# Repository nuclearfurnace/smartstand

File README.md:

# What is the SmartStand?

The SmartStand is a headphone stand that features not only a built-in, high-quality USB DAC and headphone amplifier, but the ability to detect when your headphones are in use (off the stand) and automatically switch between headphone output and line out, all while presenting as a normal USB audio device to your computer.

# What are the specifications?  How does it sound?

I'm not sure yet!  I haven't reached a rev A for the final design.  Here's the rough breakdown of what the design has:

- XMOS processor for the USB controller ([datasheet](https://www.xmos.com/download/private/XUF208-256-TQ64-Datasheet%281.10%29.pdf), can support UAC2 up to 384kHz at 2 channels)
- TI [PCM5102A](http://www.ti.com/lit/ds/symlink/pcm5102a.pdf) for the DAC
- low-noise power supplies
    - 12V DC wall wart which feeds
        - a TI [TPS563200](http://www.ti.com/lit/ds/symlink/tps563200.pdf) synchronous step-down converter which feeds
            - a TI [TPS7A8300](http://www.ti.com/lit/ds/symlink/tps7a8300.pdf) which provides the 1V0 core supply
        - a TI [TPS563200](http://www.ti.com/lit/ds/symlink/tps563200.pdf) synchronous step-down converter which feeds
            - a TI [TPS7A8300](http://www.ti.com/lit/ds/symlink/tps7a8300.pdf) which provides the digital 3V3 supply
            - a TI [TPS7A8300](http://www.ti.com/lit/ds/symlink/tps7a8300.pdf) which provides the analog 3V3 supply
        - a TI [TPS7A4701](http://www.ti.com/lit/ds/symlink/tps7a47.pdf) which provides the positive 11V0 amplifier rail
        - a TI [TPS7A3301](http://www.ti.com/lit/ds/symlink/tps7a33.pdf) which provides the negative 11V0 amplifier rail
- amplifier section that mirrors the [Objective2](http://nwavguy.blogspot.com/2011/07/o2-headphone-amp.html) headphone amplifier
    - an [NJM2068](http://www.njr.com/semicon/PDF/NJM2068_E.pdf)-based gain stage, with internal switches for dual gain settings
    - an Alps [RK14K](http://www.alps.com/prod/info/E/HTML/Potentiometer/RotaryPotentiometers/RK14K12/RK14K1240A4S.html) volume control pot after the gain stage, big and chunky (1B taper)
    - paralleled [NJM4556A](http://www.njr.com/semicon/PDF/NJM4556A_E.pdf)s for the output stage for lots o' power
- relay-based switching between headphone outputs and line outs, as well as relay-based protection on the headphone outputs to avoid pops and thumps
- Neutrik [NRJ6HH](http://www.neutrik.com/en/audio/plugs-and-jacks/slim-jacks/nrj6hh) 1/4" headphone jack
- Switchcraft [PJRAN2X1U01AUX](http://www.switchcraft.com/Drawings/pjran2x1u__x_series_cd.pdf) RCA outputs
- TE USB type B connector [292304-1](http://www.te.com/usa-en/product-292304-1.html)
- 0.1% precision resistors, and NP0/C0G capacitors in the audio path

# What's in this repository?

This repository will hold all the Eagle CAD design files for the internals, including:

- original, sloppy evaluation boards for the XMOS processor and amplifier section
- the integrated USB DAC/amplifier board (single board that will be used in the unit)
- proximity sensor board (will be located in the stand arm where the headphones rest)
- any schematic- or board-related design files i.e. DRC rules, 3D IDF data, etc

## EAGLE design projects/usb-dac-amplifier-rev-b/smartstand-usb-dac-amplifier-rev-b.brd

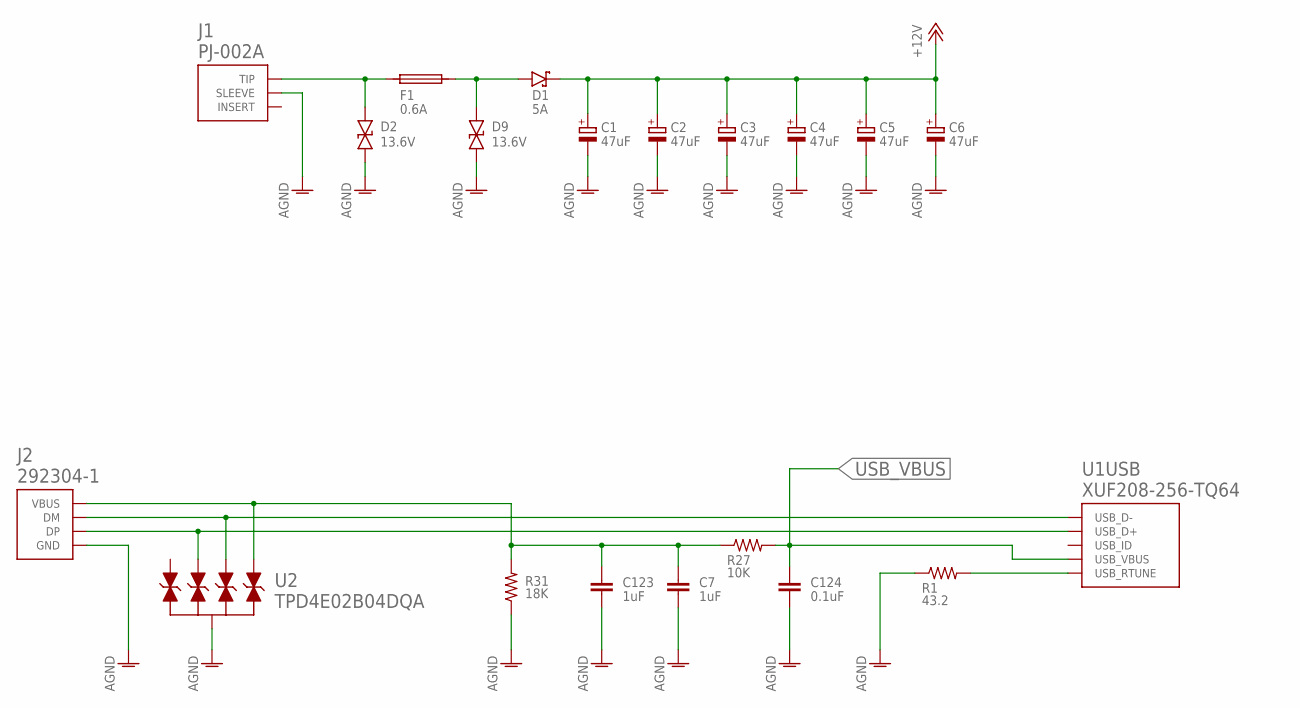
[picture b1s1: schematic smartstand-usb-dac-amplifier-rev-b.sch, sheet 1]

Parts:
C1, C2, C3, C4, C5, C6: 47uF; CHEMICON_F55
C7, C123: 1uF; C0603
C124: 0.1uF; C0402
D1: 5A; SOD128; MPN PMEG3050BEP,115
D2, D9: 13.6V; SMA; MPN P4SMA16CA
F1: 0.6A; 2920L; MPN 2920L030DR
J1: PJ-002A; VOLTAGE 12.0; MPN PJ-002A
J2: 292304-1; 292304; MPN 292304-1
R1: 43.2; R0402; MPN RK73B1ETTP430J
R27: 10K; R0402
R31: 18K; R0402
U1: XUF208-256-TQ64; TQFP-64-EXPOSED-PAD
U2: TPD4E02B04DQA; R-PUSON-N10; MPN TPD4E02B04DQAR

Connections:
+12V: C1.+, C2.+, C3.+, C4.+, C5.+, C6.+, D1.C; also elsewhere on the board
AGND: C1.-, C2.-, C3.-, C4.-, C5.-, C6.-, C7.2, C123.2, C124.2, D2.A, D9.A, J1.2 (SLEEVE), J2.P$4 (GND), R1.1, R31.1, U2.P$3 (GND), U2.P$8 (GND); also elsewhere on the board
unnamed: D2.C, F1.P$1 (1), J1.1 (TIP)
unnamed: D1.A, D9.C, F1.P$2 (2)
unnamed: R1.2, U1.P$24 (USB_RTUNE)
unnamed: C7.1, C123.1, J2.P$1 (VBUS), R27.1, R31.2, U2.P$5 (IO4), U2.P$6 (IO4)
USB_D_N: J2.P$2 (DM), U1.P$26 (USB_D-), U2.P$4 (IO3), U2.P$7 (IO3)
USB_D_P: J2.P$3 (DP), U1.P$25 (USB_D+), U2.P$2 (IO2), U2.P$9 (IO2)
USB_VBUS: C124.1, R27.2, U1.P$23 (USB_VBUS); also elsewhere on the board

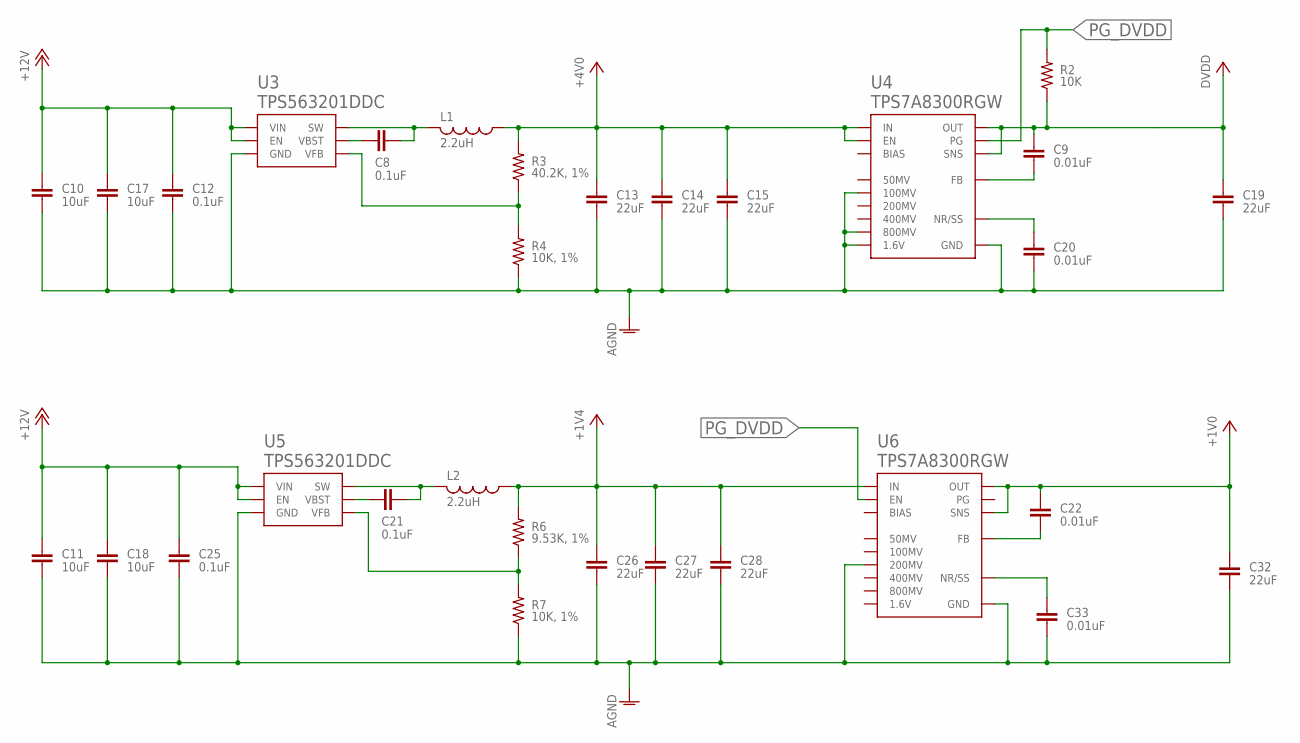
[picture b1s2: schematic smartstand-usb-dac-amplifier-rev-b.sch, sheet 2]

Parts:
C8, C21: 0.1uF; C0603; MPN GCM188R71H104KA57J
C9, C20, C22, C33: 0.01uF; C0402
C10, C11, C17, C18: 10uF; C0603; MPN GRM188R6YA106MA73D
C12, C25: 0.1uF; C0402
C13, C14, C15, C19, C26, C27, C28, C32: 22uF; C0603; MPN ZRB18AR61A226ME01L
L1, L2: 2.2uH; TDK-VLP8040; MPN VLP8040T-2R2N
R2: 10K; R0402; MPN RC0402FR-0710KL
R3: 40.2K, 1%; R0402; MPN RK73H1ETTP4022F
R4, R7: 10K, 1%; R0402; MPN RC0402FR-0710KL
R6: 9.53K, 1%; R0402; MPN RC0402FR-079K53L
U3, U5: TPS563201DDC; R-PDSO-G6-DBV; MPN TPS563201DDC
U4, U6: TPS7A8300RGW; S-PVQFN-N20; MPN TPS7A8300RGWR

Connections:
+1V0: C22.1, C32.1, U6.P$1 (OUT), U6.P$2 (SNS), U6.P$19 (OUT), U6.P$20 (OUT); also elsewhere on the board
+1V4: C26.1, C27.1, C28.1, L2.P$1 (1), R6.2, U6.P$15 (IN), U6.P$16 (IN), U6.P$17 (IN); also elsewhere on the board
+4V0: C13.1, C14.1, C15.1, L1.P$1 (1), R3.2, U4.P$14 (EN), U4.P$15 (IN), U4.P$16 (IN), U4.P$17 (IN); also elsewhere on the board
+12V: C10.1, C11.1, C12.1, C17.1, C18.1, C25.1, U3.3 (VIN), U3.5 (EN), U5.3 (VIN), U5.5 (EN); also elsewhere on the board
AGND: C10.2, C11.2, C12.2, C13.2, C14.2, C15.2, C17.2, C18.2, C19.2, C20.2, C25.2, C26.2, C27.2, C28.2, C32.2, C33.2, R4.1, R7.1, U3.1 (GND), U4.P$6 (100MV), U4.P$8 (GND), U4.P$10 (800MV), U4.P$11 (1.6V), U4.P$18 (GND), U4.P$21 (GND), U4.P$22 (GND), U4.P$23 (GND), U4.P$24 (GND), U4.P$25 (GND), U4.P$26 (GND), U4.P$27 (GND), U4.P$28 (GND), U4.P$29 (GND), U4.P$EP (GND), U5.1 (GND), U6.P$7 (200MV), U6.P$8 (GND), U6.P$18 (GND), U6.P$21 (GND), U6.P$22 (GND), U6.P$23 (GND), U6.P$24 (GND), U6.P$25 (GND), U6.P$26 (GND), U6.P$27 (GND), U6.P$28 (GND), U6.P$29 (GND), U6.P$EP (GND); also elsewhere on the board
DVDD: C9.1, C19.1, R2.1, U4.P$1 (OUT), U4.P$2 (SNS), U4.P$19 (OUT), U4.P$20 (OUT); also elsewhere on the board
unnamed: C20.1, U4.P$13 (NR/SS)
unnamed: C9.2, U4.P$3 (FB)
unnamed: C8.2, L1.P$2 (2), U3.2 (SW)
unnamed: C8.1, U3.6 (VBST)
unnamed: R3.1, R4.2, U3.4 (VFB)
unnamed: C21.2, L2.P$2 (2), U5.2 (SW)
unnamed: C21.1, U5.6 (VBST)
unnamed: R6.1, R7.2, U5.4 (VFB)
unnamed: C33.1, U6.P$13 (NR/SS)
unnamed: C22.2, U6.P$3 (FB)
PG_DVDD: R2.2, U4.P$4 (PG), U6.P$14 (EN)

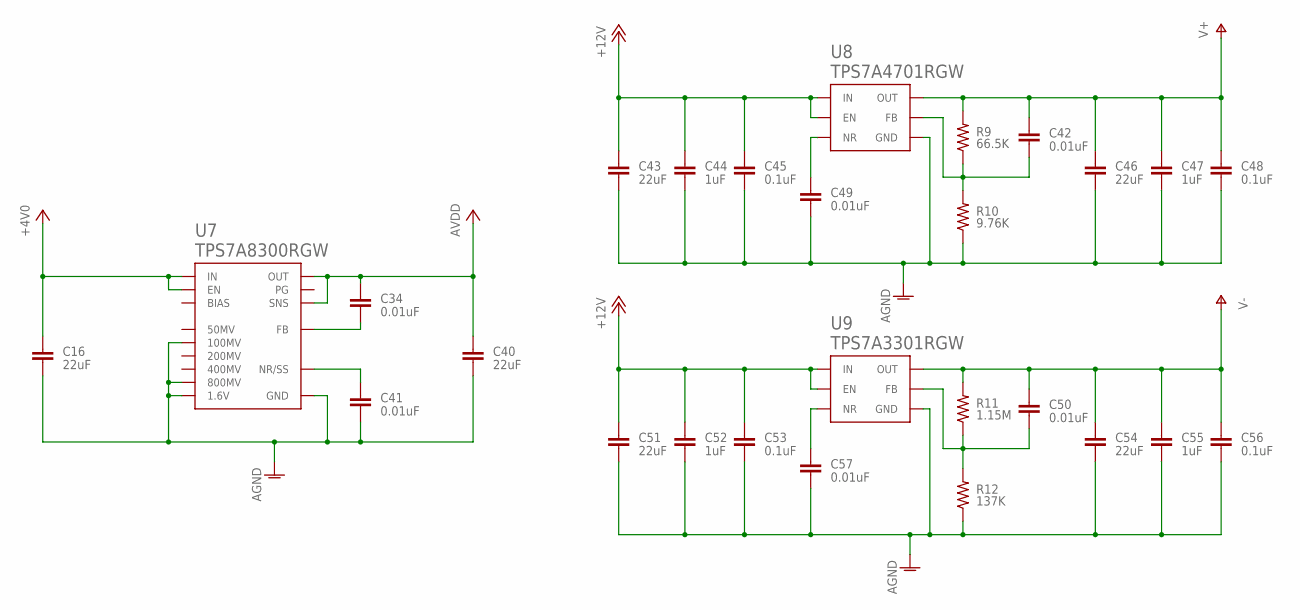
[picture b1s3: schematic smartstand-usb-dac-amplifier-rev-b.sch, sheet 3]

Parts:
C16, C40: 22uF; C0603; MPN ZRB18AR61A226ME01L
C34, C41, C42, C49, C50, C57: 0.01uF; C0402
C43, C46, C51, C54: 22uF; C0603; MPN GRM188R6YA106MA73D
C44, C47, C52, C55: 1uF; C0603
C45, C48, C53, C56: 0.1uF; C0402
R9: 66.5K; R0402; MPN RK73H1ETTP6652F
R10: 9.76K; R0402; MPN RC0402FR-079K76L
R11: 1.15M; R0402; MPN RK73H1ETTP1154F
R12: 137K; R0402; MPN RC0402FR-07137KL
U7: TPS7A8300RGW; S-PVQFN-N20; MPN TPS7A8300RGWR
U8: TPS7A4701RGW; S-PVQFN-N20; MPN TPS7A4701RGWR
U9: TPS7A3301RGW; S-PVQFN-N20; MPN TPS7A3301RGWR

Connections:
+4V0: C16.1, U7.P$14 (EN), U7.P$15 (IN), U7.P$16 (IN), U7.P$17 (IN); also elsewhere on the board
+12V: C43.1, C44.1, C45.1, C51.1, C52.1, C53.1, U8.P$13 (EN), U8.P$15 (IN), U8.P$16 (IN), U9.P$13 (EN), U9.P$15 (IN), U9.P$16 (IN); also elsewhere on the board
AGND: C16.2, C40.2, C41.2, C43.2, C44.2, C45.2, C46.2, C47.2, C48.2, C49.2, C51.2, C52.2, C53.2, C54.2, C55.2, C56.2, C57.2, R10.1, R12.1, U7.P$6 (100MV), U7.P$8 (GND), U7.P$10 (800MV), U7.P$11 (1.6V), U7.P$18 (GND), U7.P$21 (GND), U7.P$22 (GND), U7.P$23 (GND), U7.P$24 (GND), U7.P$25 (GND), U7.P$26 (GND), U7.P$27 (GND), U7.P$28 (GND), U7.P$29 (GND), U7.P$EP (GND), U8.P$7 (GND), U8.P$17 (GND), U8.P$18 (GND), U8.P$19 (GND), U8.P$21 (GND), U8.P$22 (GND), U8.P$23 (GND), U8.P$24 (GND), U8.P$25 (GND), U8.P$26 (GND), U8.P$27 (GND), U8.P$28 (GND), U8.P$29 (GND), U8.P$EP (GND), U9.P$7 (GND), U9.P$17 (GND), U9.P$18 (GND), U9.P$19 (GND), U9.P$21 (GND), U9.P$22 (GND), U9.P$23 (GND), U9.P$24 (GND), U9.P$25 (GND), U9.P$26 (GND), U9.P$27 (GND), U9.P$28 (GND), U9.P$29 (GND), U9.P$EP (GND); also elsewhere on the board
AVDD: C34.1, C40.1, U7.P$1 (OUT), U7.P$2 (SNS), U7.P$19 (OUT), U7.P$20 (OUT); also elsewhere on the board
unnamed: C57.1, U9.P$14 (NR)
unnamed: C49.1, U8.P$14 (NR)
unnamed: C42.2, R9.1, R10.2, U8.P$3 (FB)
unnamed: C50.2, R11.1, R12.2, U9.P$3 (FB)
unnamed: C41.1, U7.P$13 (NR/SS)
unnamed: C34.2, U7.P$3 (FB)
V+: C42.1, C46.1, C47.1, C48.1, R9.2, U8.P$1 (OUT), U8.P$20 (OUT); also elsewhere on the board
V-: C50.1, C54.1, C55.1, C56.1, R11.2, U9.P$1 (OUT), U9.P$20 (OUT); also elsewhere on the board

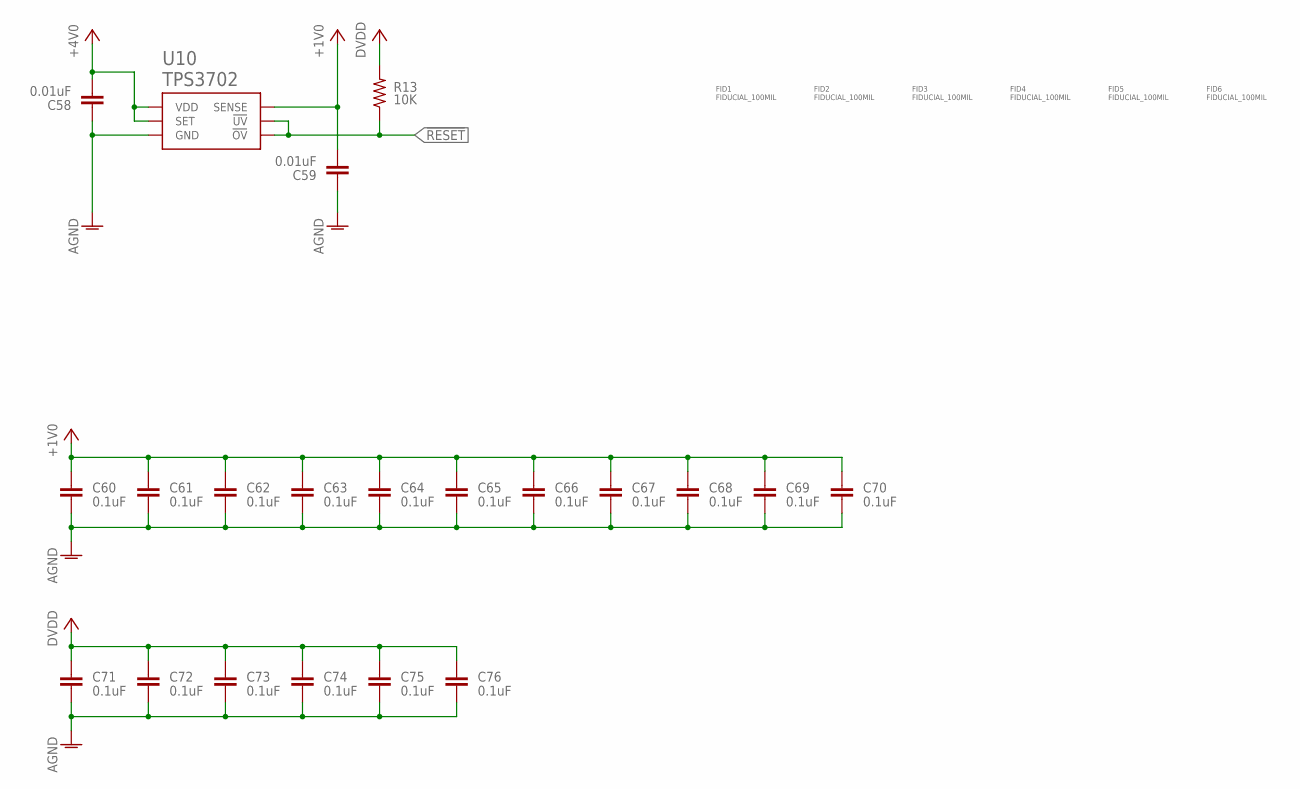
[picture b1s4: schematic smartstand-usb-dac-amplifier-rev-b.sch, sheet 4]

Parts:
C58, C59: 0.01uF; C0402
C60, C61, C62, C63, C64, C65, C66, C67, C68, C69, C70, C71, C72, C73, C74, C75, C76: 0.1uF; C0402
FID1, FID2, FID3, FID4, FID5, FID6: FIDUCIAL_100MIL
R13: 10K; R0402
U10: TPS3702; R-PDSO-G6-DBV; MPN TPS3702CX10DDCT

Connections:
!RESET: R13.1, U10.1 (!UV), U10.6 (!OV); also elsewhere on the board
+1V0: C59.2, C60.1, C61.1, C62.1, C63.1, C64.1, C65.1, C66.1, C67.1, C68.1, C69.1, C70.1, U10.3 (SENSE); also elsewhere on the board
+4V0: C58.2, U10.4 (SET), U10.5 (VDD); also elsewhere on the board
AGND: C58.1, C59.1, C60.2, C61.2, C62.2, C63.2, C64.2, C65.2, C66.2, C67.2, C68.2, C69.2, C70.2, C71.2, C72.2, C73.2, C74.2, C75.2, C76.2, U10.2 (GND); also elsewhere on the board
DVDD: C71.1, C72.1, C73.1, C74.1, C75.1, C76.1, R13.2; also elsewhere on the board

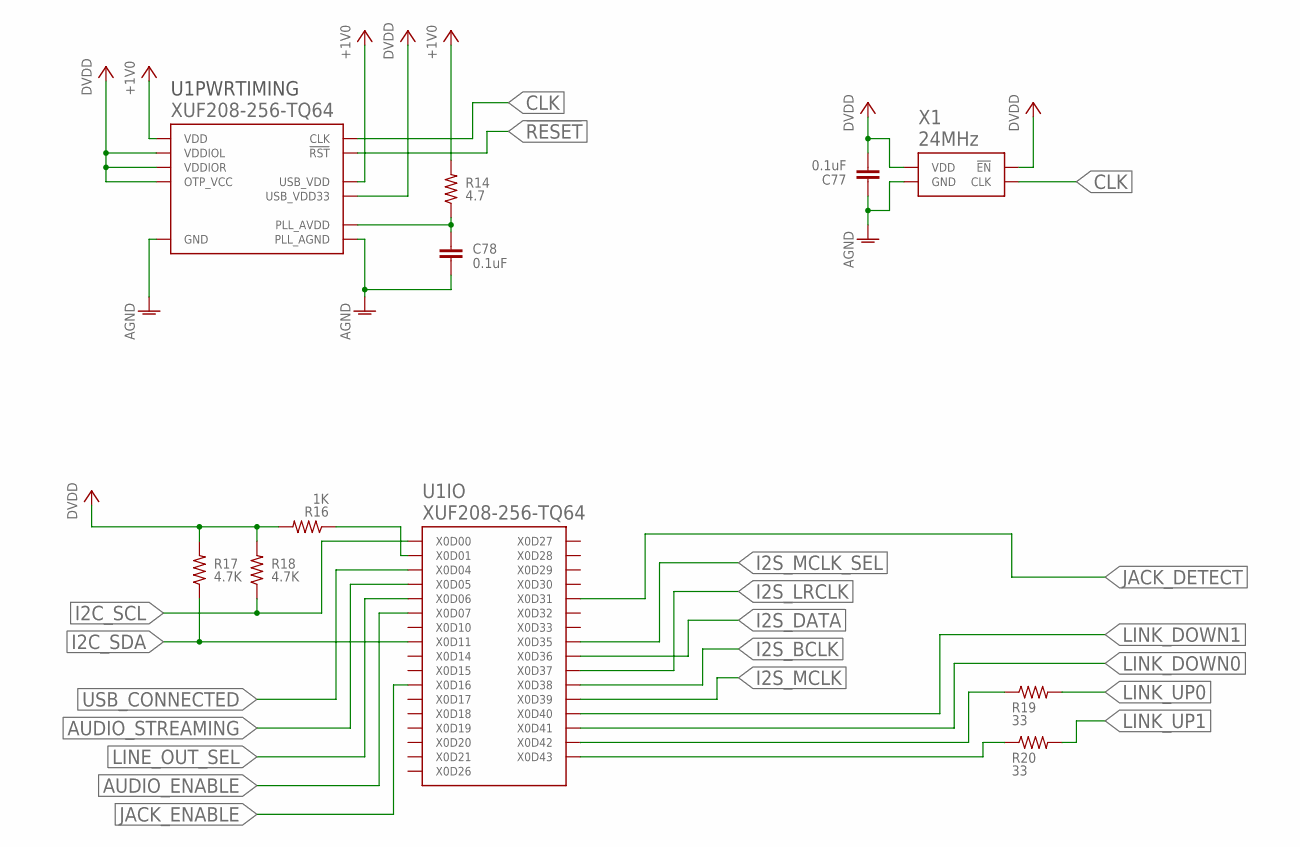
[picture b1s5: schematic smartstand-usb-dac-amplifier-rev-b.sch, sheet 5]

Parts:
C77, C78: 0.1uF; C0402
R14: 4.7; R0402; MPN RCS04024R70JNED
R16: 1K; R0402
R17, R18: 4.7K; R0402
R19, R20: 33; R0402; MPN RK73B1ETTP330J
U1: XUF208-256-TQ64; TQFP-64-EXPOSED-PAD
X1: 24MHz; KC2520C; MPN KC2520C24.0000C2LE00

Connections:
!RESET: U1.P$57 (!RST); also elsewhere on the board
+1V0: R14.2, U1.P$9 (VDD), U1.P$10 (VDD), U1.P$20 (VDD), U1.P$27 (USB_VDD), U1.P$31 (VDD), U1.P$39 (VDD), U1.P$40 (VDD), U1.P$41 (VDD), U1.P$52 (VDD), U1.P$56 (VDD), U1.P$59 (VDD); also elsewhere on the board
AGND: C77.1, C78.2, U1.P$54 (PLL_AGND), U1.P$65 (GND), U1.P$66 (GND), U1.P$67 (GND), U1.P$68 (GND), U1.P$69 (GND), U1.P$70 (GND), U1.P$71 (GND), U1.P$72 (GND), U1.P$73 (GND), U1.P$74 (GND), X1.P$2 (GND); also elsewhere on the board
AUDIO_ENABLE: U1.P$19 (X0D07); also elsewhere on the board
AUDIO_STREAMING: U1.P$17 (X0D05); also elsewhere on the board
CLK: U1.P$58 (CLK), X1.P$3 (CLK); also elsewhere on the board
DVDD: C77.2, R16.2, R17.2, R18.2, U1.P$3 (VDDIOL), U1.P$13 (VDDIOL), U1.P$22 (USB_VDD33), U1.P$34 (VDDIOR), U1.P$44 (VDDIOR), U1.P$55 (OTP_VCC), X1.P$1 (!EN), X1.P$4 (VDD); also elsewhere on the board
I2C_SCL: R18.1, U1.P$14 (X0D00); also elsewhere on the board
I2C_SDA: R17.1, U1.P$16 (X0D11); also elsewhere on the board
I2S_BCLK: U1.P$2 (X0D38); also elsewhere on the board
I2S_DATA: U1.P$1 (X0D36); also elsewhere on the board
I2S_LRCLK: U1.P$64 (X0D37); also elsewhere on the board
I2S_MCLK: U1.P$4 (X0D39); also elsewhere on the board
I2S_MCLK_SEL: U1.P$42 (X0D35); also elsewhere on the board
JACK_DETECT: U1.P$51 (X0D31); also elsewhere on the board
JACK_ENABLE: U1.P$35 (X0D16); also elsewhere on the board
LINE_OUT_SEL: U1.P$18 (X0D06); also elsewhere on the board
LINK_DOWN0: U1.P$6 (X0D41); also elsewhere on the board
LINK_DOWN1: U1.P$5 (X0D40); also elsewhere on the board
LINK_UP0: R19.2; also elsewhere on the board
LINK_UP1: R20.2; also elsewhere on the board
unnamed: R19.1, U1.P$7 (X0D42)
unnamed: R20.1, U1.P$8 (X0D43)
unnamed: R16.1, U1.P$11 (X0D01)
PLL_AVDD: C78.1, R14.1, U1.P$53 (PLL_AVDD); also elsewhere on the board
USB_CONNECTED: U1.P$15 (X0D04); also elsewhere on the board

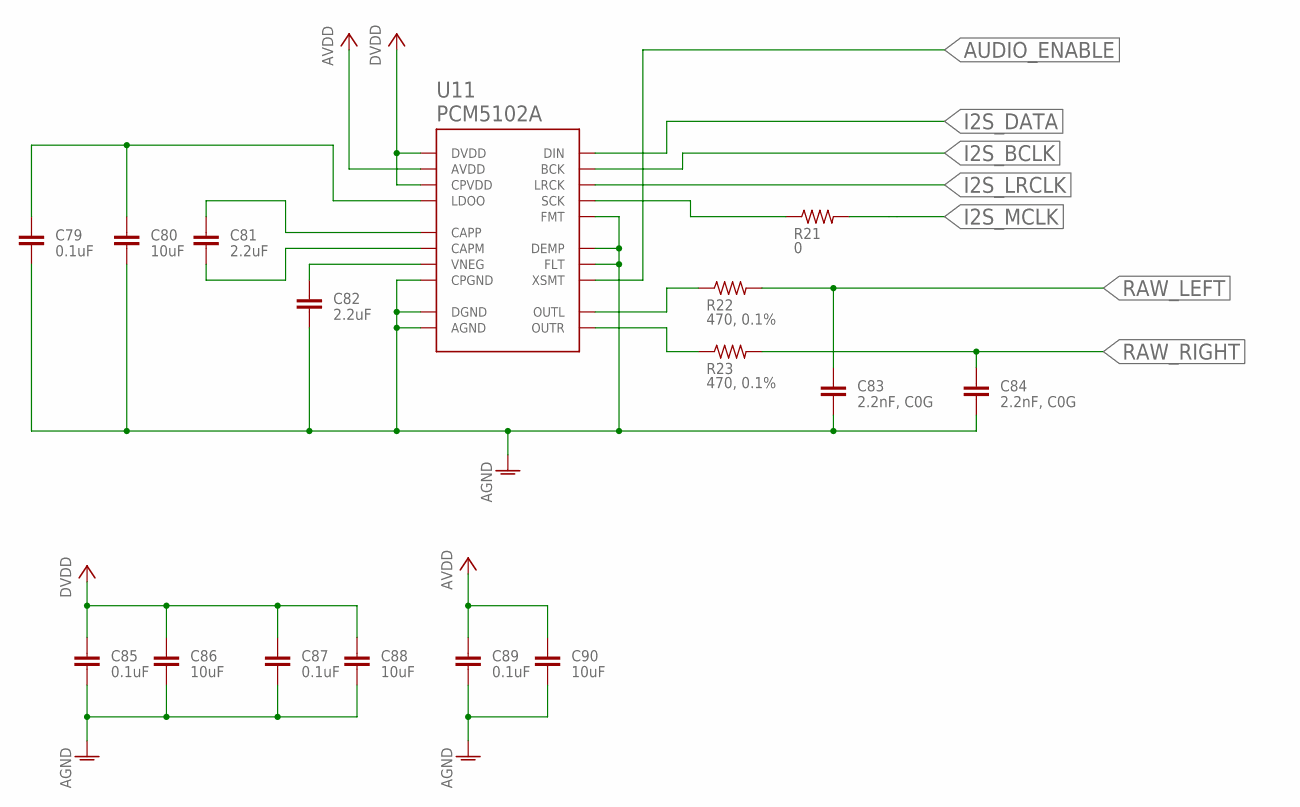
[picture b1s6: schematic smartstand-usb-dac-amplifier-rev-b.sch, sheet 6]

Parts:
C79, C85, C87, C89: 0.1uF; C0402
C80, C86, C88, C90: 10uF; C0805; MPN GRM21BR61E106KA73L
C81, C82: 2.2uF; C0603; MPN GRM188R61C225KE15D
C83, C84: 2.2nF, C0G; C0402; MPN C0402C222J3GACTU
R21: 0; R0402
R22, R23: 470, 0.1%; R0402; MPN RG1005P-471-B-T5
U11: PCM5102A; R-PDSO-G20; MPN PCM5102APWR

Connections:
AGND: C79.2, C80.2, C82.2, C83.2, C84.2, C85.2, C86.2, C87.2, C88.2, C89.2, C90.2, U11.P$3 (CPGND), U11.P$9 (AGND), U11.P$10 (DEMP), U11.P$11 (FLT), U11.P$16 (FMT), U11.P$19 (DGND); also elsewhere on the board
AUDIO_ENABLE: U11.P$17 (XSMT); also elsewhere on the board
AVDD: C89.1, C90.1, U11.P$8 (AVDD); also elsewhere on the board
DVDD: C85.1, C86.1, C87.1, C88.1, U11.P$1 (CPVDD), U11.P$20 (DVDD); also elsewhere on the board
I2S_BCLK: U11.P$13 (BCK); also elsewhere on the board
I2S_DATA: U11.P$14 (DIN); also elsewhere on the board
I2S_LRCLK: U11.P$15 (LRCK); also elsewhere on the board
I2S_MCLK: R21.2; also elsewhere on the board
unnamed: C81.1, U11.P$2 (CAPP)
unnamed: C81.2, U11.P$4 (CAPM)
unnamed: C82.1, U11.P$5 (VNEG)
unnamed: C79.1, C80.1, U11.P$18 (LDOO)
unnamed: R22.1, U11.P$6 (OUTL)
unnamed: R23.1, U11.P$7 (OUTR)
unnamed: R21.1, U11.P$12 (SCK)
RAW_LEFT: C83.1, R22.2; also elsewhere on the board
RAW_RIGHT: C84.1, R23.2; also elsewhere on the board

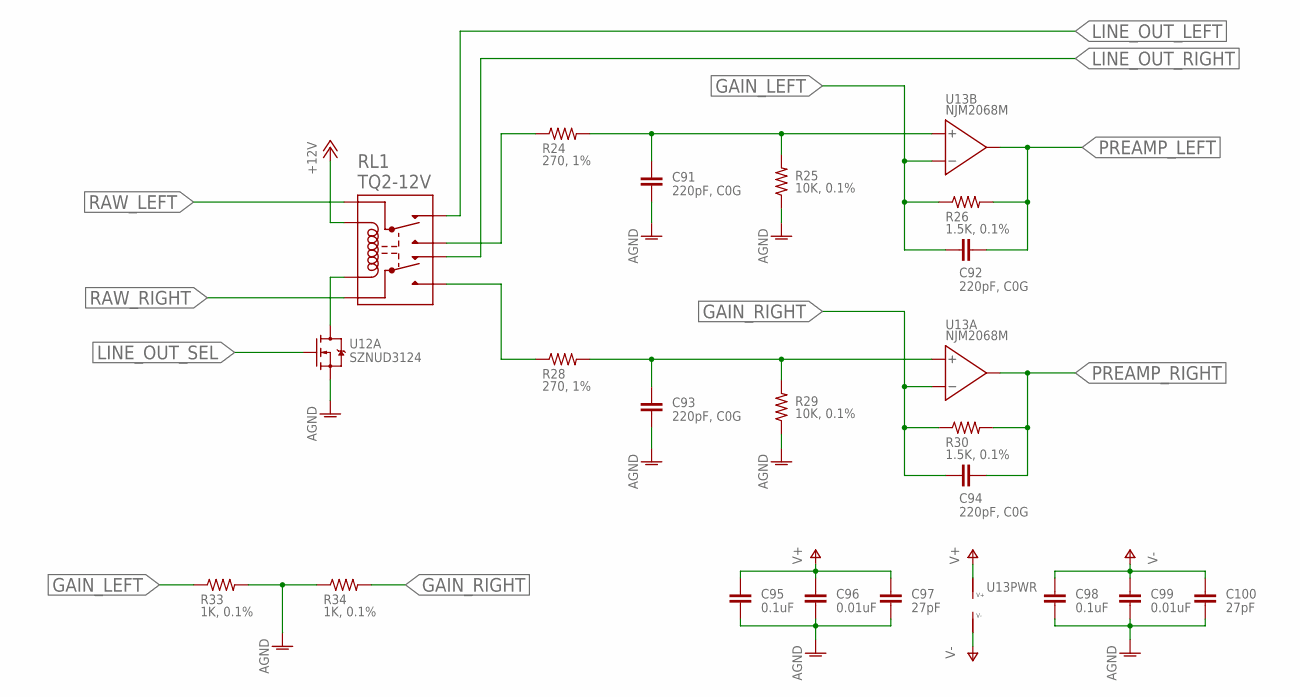
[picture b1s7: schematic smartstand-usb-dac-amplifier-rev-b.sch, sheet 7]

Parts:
C91, C92, C93, C94: 220pF, C0G; C0402; MPN GRM1555C1H221JA01J
C95, C98: 0.1uF; C0402
C96, C99: 0.01uF; C0402
C97, C100: 27pF; C0402
R24, R28: 270, 1%; R0603; MPN MCT06030C2700FP500
R25, R29: 10K, 0.1%; R0603; MPN MCT06030C1002FP500
R26, R30: 1.5K, 0.1%; R0603; MPN MCT06030C1501FP500
R33, R34: 1K, 0.1%; R0603; MPN MCT06030C1001FP500
RL1: TQ2-12V; TQ2; MPN TQ2-12V
U12: SZNUD3124; SOT-457; MPN SZNUD3124DMT1G
U13: NJM2068M; DMP8; MPN NJM2068M-TE1

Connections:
+12V: RL1.P$1 (COIL_P); also elsewhere on the board
AGND: C91.2, C93.2, C95.2, C96.2, C97.2, C98.2, C99.2, C100.2, R25.1, R29.1, R33.2, R34.1, U12.1 (S); also elsewhere on the board
GAIN_LEFT: C92.1, R26.1, R33.1, U13.P$6 (-IN)
GAIN_RIGHT: C94.1, R30.1, R34.2, U13.P$2 (-IN)
LINE_OUT_LEFT: RL1.P$2 (NC1); also elsewhere on the board
LINE_OUT_RIGHT: RL1.P$9 (NC2); also elsewhere on the board
LINE_OUT_SEL: U12.2 (G); also elsewhere on the board
unnamed: RL1.P$10 (COIL_N), U12.6 (D)
unnamed: C93.1, R28.2, R29.2, U13.P$3 (+IN)
unnamed: C91.1, R24.2, R25.2, U13.P$5 (+IN)
unnamed: R28.1, RL1.P$7 (NO2)
unnamed: R24.1, RL1.P$4 (NO1)
PREAMP_LEFT: C92.2, R26.2, U13.P$7 (OUT); also elsewhere on the board
PREAMP_RIGHT: C94.2, R30.2, U13.P$1 (OUT); also elsewhere on the board
RAW_LEFT: RL1.P$3 (COM1); also elsewhere on the board
RAW_RIGHT: RL1.P$8 (COM2); also elsewhere on the board
V+: C95.1, C96.1, C97.1, U13.P$8 (V+); also elsewhere on the board
V-: C98.1, C99.1, C100.1, U13.P$4 (V-); also elsewhere on the board

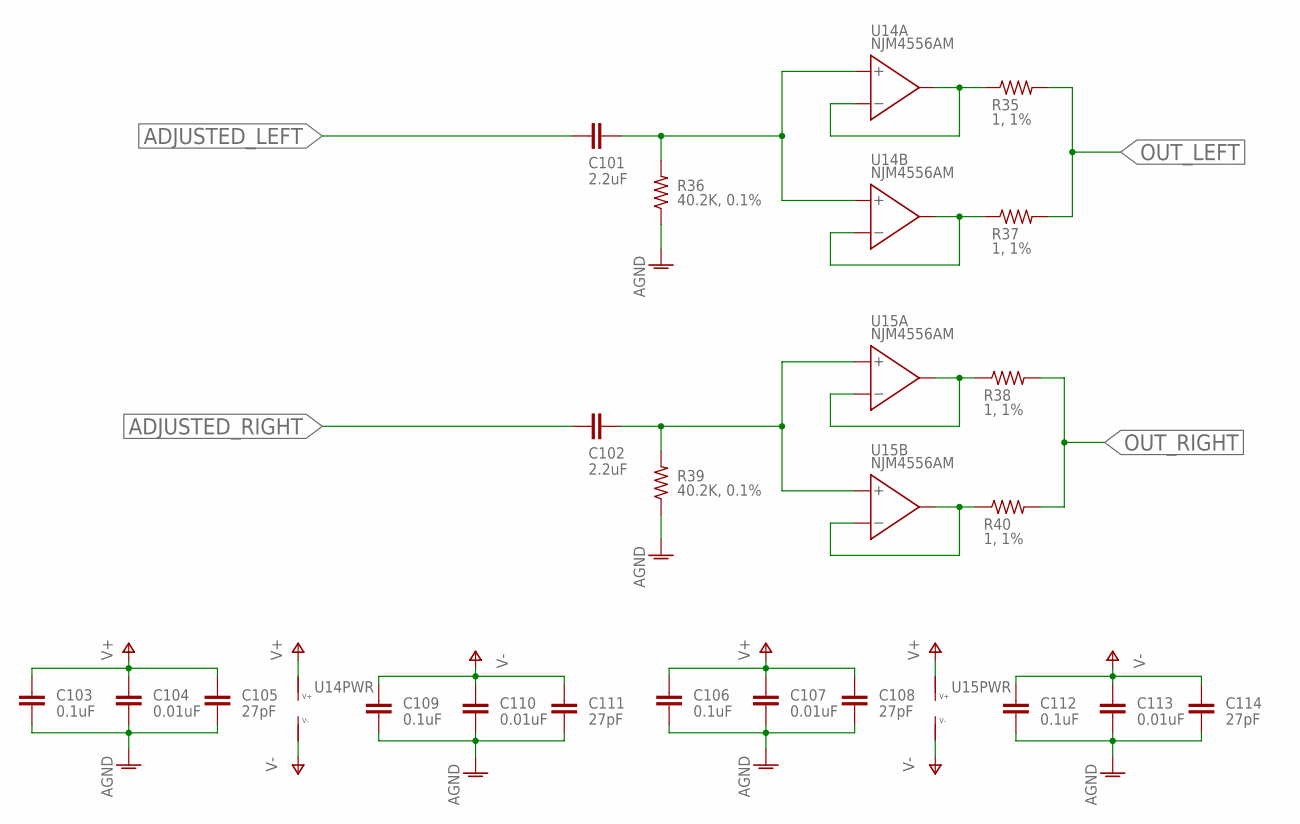
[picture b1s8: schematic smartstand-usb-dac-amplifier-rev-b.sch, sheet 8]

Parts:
C101, C102: 2.2uF; KEMET-5MM-6.0-7.2; MPN RSBCC4220Z310K
C103, C106, C109, C112: 0.1uF; C0402
C104, C107, C110, C113: 0.01uF; C0402
C105, C108, C111, C114: 27pF; C0402
R35, R37, R38, R40: 1, 1%; R1206; MPN MCA12060C1008FP500
R36, R39: 40.2K, 0.1%; R0402; MPN RG1005P-4022-B-T5
U14, U15: NJM4556AM; DMP8; MPN NJM4556AM-TE1

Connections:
ADJUSTED_LEFT: C101.P$1 (1); also elsewhere on the board
ADJUSTED_RIGHT: C102.P$1 (1); also elsewhere on the board
AGND: C103.2, C104.2, C105.2, C106.2, C107.2, C108.2, C109.2, C110.2, C111.2, C112.2, C113.2, C114.2, R36.1, R39.1; also elsewhere on the board
unnamed: C101.P$2 (2), R36.2, U14.P$3 (+IN), U14.P$5 (+IN)
unnamed: C102.P$2 (2), R39.2, U15.P$3 (+IN), U15.P$5 (+IN)
unnamed: R35.1, U14.P$1 (OUT), U14.P$2 (-IN)
unnamed: R37.1, U14.P$6 (-IN), U14.P$7 (OUT)
unnamed: R38.1, U15.P$1 (OUT), U15.P$2 (-IN)
unnamed: R40.1, U15.P$6 (-IN), U15.P$7 (OUT)
OUT_LEFT: R35.2, R37.2; also elsewhere on the board
OUT_RIGHT: R38.2, R40.2; also elsewhere on the board
V+: C103.1, C104.1, C105.1, C106.1, C107.1, C108.1, U14.P$8 (V+), U15.P$8 (V+); also elsewhere on the board
V-: C109.1, C110.1, C111.1, C112.1, C113.1, C114.1, U14.P$4 (V-), U15.P$4 (V-); also elsewhere on the board

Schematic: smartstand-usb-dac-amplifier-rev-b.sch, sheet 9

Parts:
C115, C118: 1uF; C0603
C116, C119, C121: 0.1uF; C0402
C117, C120: 0.01uF; C0402
R41, R42: 0; R0402
R43: 100K; R0402
U16: TS5A3159DBV; R-PDSO-G6-DBV; MPN TS5A3159DBVR
X2: 22.5792MHz; KC2520C; MPN KC2520K22.5792C1GE00
X3: 24.576MHz; KC2520C; MPN KC2520K24.5760C1GE00

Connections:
AGND: C115.2, C116.2, C117.2, C118.2, C119.2, C120.2, C121.2, R43.1, U16.2 (GND), X2.P$2 (GND), X3.P$2 (GND); also elsewhere on the board
DVDD: C115.1, C116.1, C117.1, C118.1, C119.1, C120.1, C121.1, U16.5 (V+), X2.P$1 (!EN), X2.P$4 (VDD), X3.P$1 (!EN), X3.P$4 (VDD); also elsewhere on the board
I2S_MCLK: U16.4 (COM); also elsewhere on the board
I2S_MCLK_48: R42.2, X3.P$3 (CLK)
I2S_MCLK_441: R41.2, X2.P$3 (CLK)
I2S_MCLK_SEL: R43.2, U16.6 (IN); also elsewhere on the board
unnamed: R41.1, U16.1 (NO)
unnamed: R42.1, U16.3 (NC)

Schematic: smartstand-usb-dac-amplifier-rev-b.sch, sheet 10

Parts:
C122: 0.1uF; C0402
J3: NRJ6HH; MPN NRJ6HH
J4: PJRAN2X1U01AUX; PJRAN2X1U; MPN PJRAN2X1U01AUX
R45: 100K; R0402
R46: 10K; R0402
R47: 49.9K; R0402; MPN RC0402FR-0749K9L
RL2: TQ2-12V; TQ2; MPN TQ2-12V
U12: SZNUD3124; SOT-457; MPN SZNUD3124DMT1G
U18, U19: TPD2E007DCK; R-PDSO-G3; MPN TPD2E007DCKR

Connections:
+12V: RL2.P$1 (COIL_P); also elsewhere on the board
AGND: C122.2, J3.S (SLEEVE), J4.L_SLEEVE (SLEEVE), J4.R_SLEEVE (SLEEVE), R46.1, RL2.P$2 (NC1), RL2.P$9 (NC2), U12.4 (S), U18.3 (GND), U19.3 (GND); also elsewhere on the board
DVDD: R45.2; also elsewhere on the board
JACK_DETECT: C122.1, R47.2; also elsewhere on the board
JACK_ENABLE: U12.5 (G); also elsewhere on the board
LINE_OUT_LEFT: J4.L_TIP (TIP), U19.2 (IO2); also elsewhere on the board
LINE_OUT_RIGHT: J4.R_TIP (TIP), U19.1 (IO1); also elsewhere on the board
unnamed: J3.T (TIP), R46.2, RL2.P$3 (COM1), U18.2 (IO2)
unnamed: J3.R (RING), RL2.P$8 (COM2), U18.1 (IO1)
unnamed: RL2.P$10 (COIL_N), U12.3 (D)
unnamed: J3.TN (T_SENSE), R45.1, R47.1
OUT_LEFT: RL2.P$4 (NO1); also elsewhere on the board
OUT_RIGHT: RL2.P$7 (NO2); also elsewhere on the board

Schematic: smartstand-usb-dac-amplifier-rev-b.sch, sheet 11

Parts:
D3, D4, D5, D6, D7, D8: 1.8V, 10mA; DIALIGHT-0603; MPN 598-8070-107F
R48: 330; R0402
R49, R50, R51, R52, R53: 220; R0402
U17: SN74LVC3G34DCU; R-PDSO-G8-DCU; MPN SN74LVC3G34DCUT

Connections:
AGND: R48.1, R49.1, R50.1, R51.1, R52.1, R53.1, U17.4 (GND); also elsewhere on the board
AUDIO_STREAMING: U17.3 (A); also elsewhere on the board
AVDD: D8.1 (A); also elsewhere on the board
DVDD: D5.1 (A), U17.8 (VDD); also elsewhere on the board
LINE_OUT_SEL: U17.6 (A); also elsewhere on the board
unnamed: D8.2 (C), R53.2
unnamed: D3.2 (C), R48.2
unnamed: D5.2 (C), R50.2
unnamed: D4.1 (A), U17.7 (Y)
unnamed: D4.2 (C), R49.2
unnamed: D6.1 (A), U17.5 (Y)
unnamed: D6.2 (C), R51.2
unnamed: D7.1 (A), U17.2 (Y)
unnamed: D7.2 (C), R52.2
USB_CONNECTED: U17.1 (A); also elsewhere on the board
USB_VBUS: D3.1 (A); also elsewhere on the board

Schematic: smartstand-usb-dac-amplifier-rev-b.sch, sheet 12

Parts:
J5: T1M-5POS; T1M-SINGLE-5POS; MPN T1M-05-T-S-RA-TR
JP1: PINHD-1X10; 1X10
JP2: PINHD-2X10; 2X10; MPN N2520-5002RB
TP1, TP2, TP3, TP4, TP5, TP6, TP7, TP8, TP9, TP10: TESTPOINT-WITH-GND; TESTPOINT-1.5-WITH-GND
U1: XUF208-256-TQ64; TQFP-64-EXPOSED-PAD

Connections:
!RESET: JP2.15; also elsewhere on the board
+1V0: TP8.S; also elsewhere on the board
+1V4: TP7.S; also elsewhere on the board
+4V0: TP3.S; also elsewhere on the board
+12V: JP1.1, TP2.S; also elsewhere on the board
ADJUSTED_LEFT: JP1.6; also elsewhere on the board
ADJUSTED_RIGHT: JP1.5; also elsewhere on the board
AGND: J5.1, J5.5, JP1.2, JP1.7, JP2.4, JP2.8, JP2.12, JP2.16, JP2.20, TP1.G, TP2.G, TP3.G, TP4.G, TP5.G, TP6.G, TP7.G, TP8.G, TP9.G, TP10.G; also elsewhere on the board
AVDD: TP5.S; also elsewhere on the board
CLK: TP1.S; also elsewhere on the board
DVDD: J5.2, JP1.8, TP6.S; also elsewhere on the board
I2C_SCL: J5.4, JP1.10; also elsewhere on the board
I2C_SDA: J5.3, JP1.9; also elsewhere on the board
LINK_DOWN0: JP2.14; also elsewhere on the board
LINK_DOWN1: JP2.18; also elsewhere on the board
LINK_UP0: JP2.10; also elsewhere on the board
LINK_UP1: JP2.6; also elsewhere on the board
unnamed: JP2.7, U1.P$60 (TMS)
unnamed: JP2.9, U1.P$61 (TCK)
unnamed: JP2.5, U1.P$62 (TDI)
unnamed: JP2.13, U1.P$63 (TDO)
PLL_AVDD: TP4.S; also elsewhere on the board
PREAMP_LEFT: JP1.3; also elsewhere on the board
PREAMP_RIGHT: JP1.4; also elsewhere on the board
V+: TP9.S; also elsewhere on the board
V-: TP10.S; also elsewhere on the board

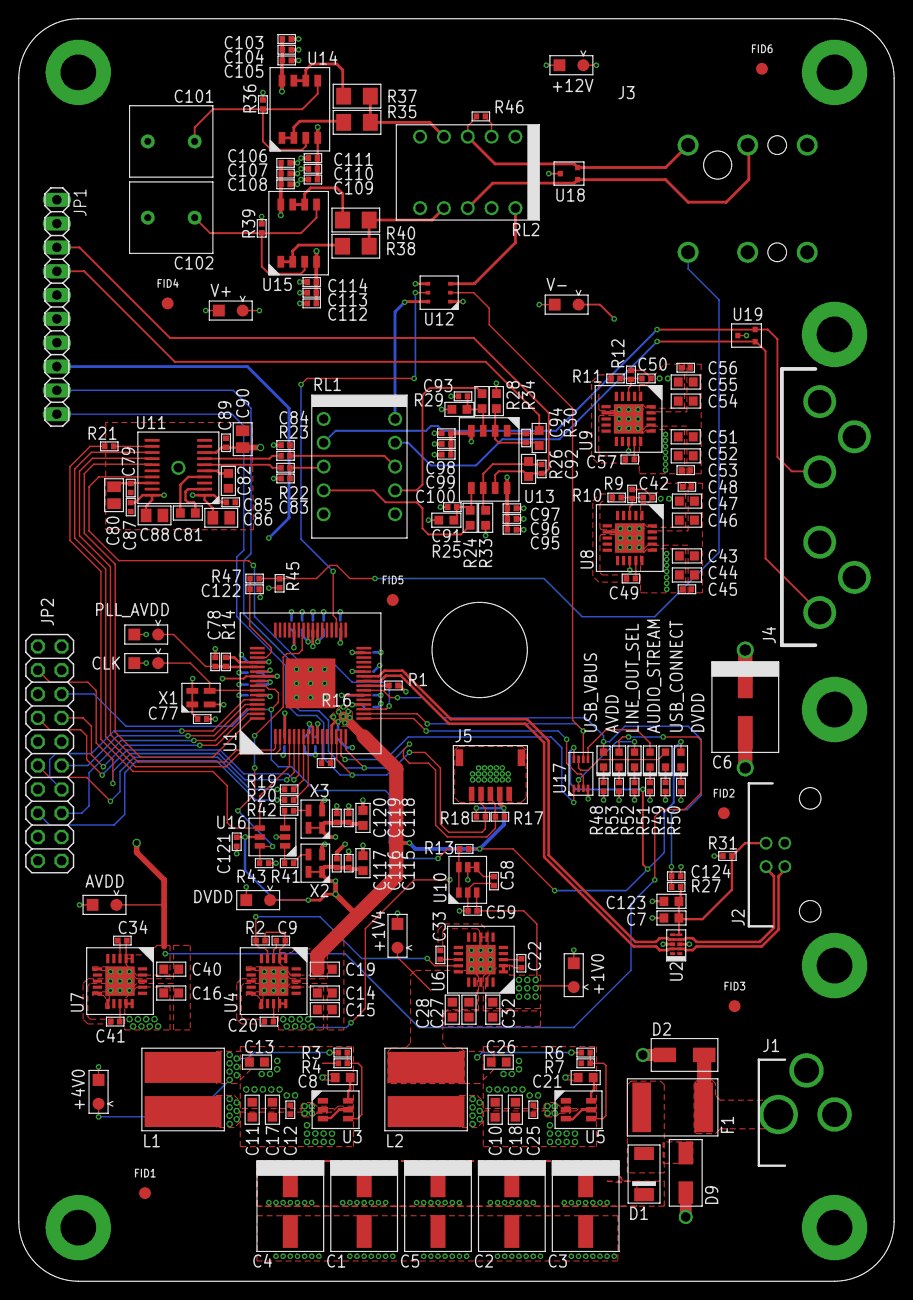
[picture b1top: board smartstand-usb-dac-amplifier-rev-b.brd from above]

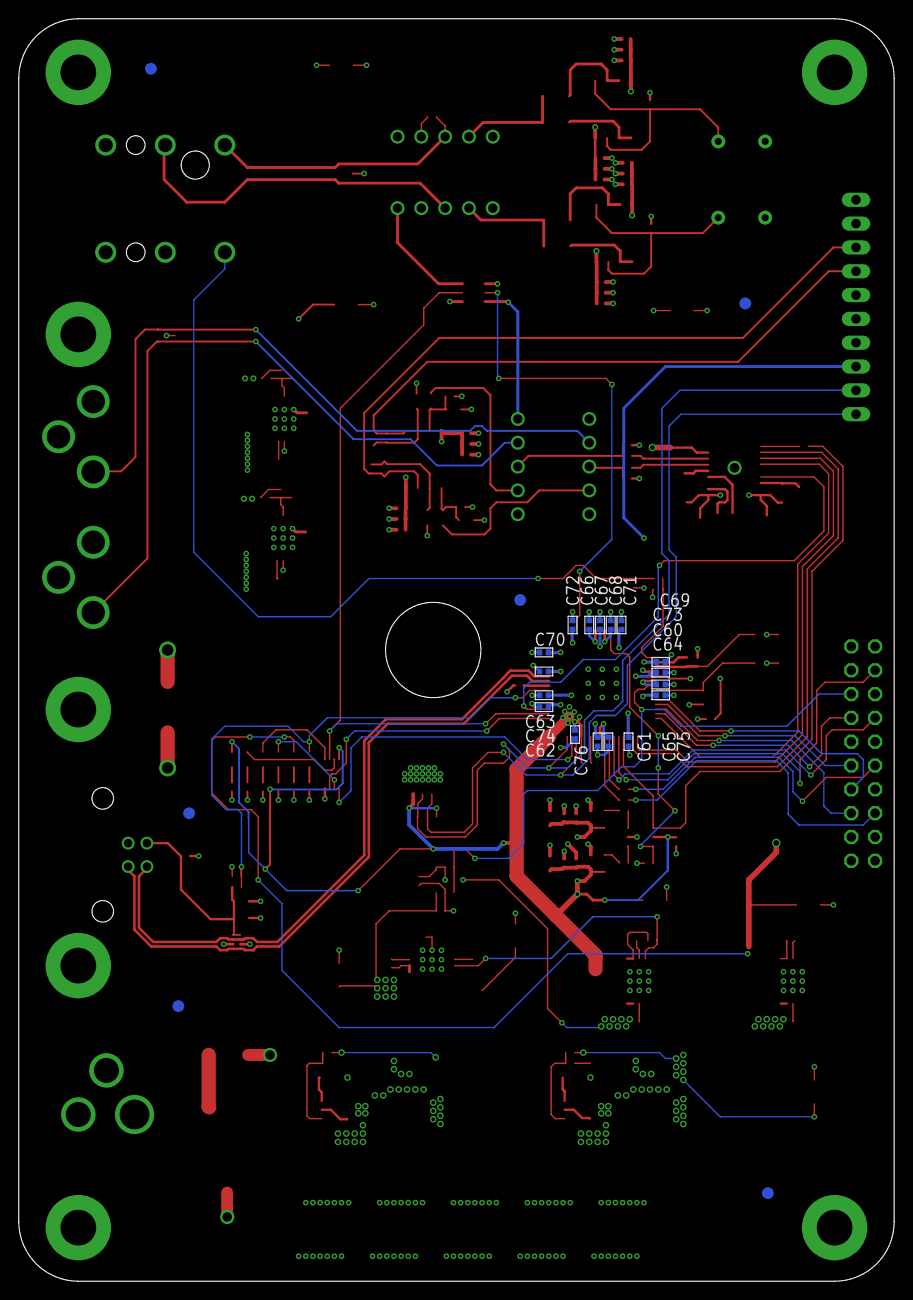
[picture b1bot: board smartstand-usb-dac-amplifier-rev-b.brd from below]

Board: 4 copper layers, 93.3 x 134.6 mm, 221 parts (17 on the bottom side), 107 nets.
